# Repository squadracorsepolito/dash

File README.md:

Benvenuti nella repository ufficiale certificata contenente i file utilizzati per la scheda NuovaDash22© utilizzata dal team Squadra Corse Driverless nell'anno 2021/22

Repository mantenuta da Matteo Bonora (Software) e Francesco Minichelli (Hardware e Software)

## How to use the makefile
This project is generated to work with bare makefiles instead of the STM32CubeIDE. In order to successfully use the makefiles, you need to have a few tools installed. Refer to [this](https://www.bonnee.me/blog/stm32-vscode/) guide on how to setup your environment and install the needed tools (Visual Studio Code is optional and only needed to do debugging and to regenerate the makefile after regenerating code through STM32CubeMX).

If you want to **flash over CAN-bus**, you will need an [additional tool](https://github.com/arkku/srec) to convert the `.bin` firmware file to `.srec` and [bootcommander](https://www.feaser.com/openblt/doku.php?id=manual:bootcommander) to send the firmware to the dashboard.

### Build
In order to build the project, issue the following command:
`make -f STM32Make.make`
You can call `make clean` to clean the build directory.

### Flash
To configure the `can0` interface on your computer, you can call `make can` with root privileges.

`make canflash` will automatically convert the firmware to Motorola S-Record and pass it to bootcommander. If you only want to have the `.srec` file, you can call `make srec`

## Configurazione STM32CubeIDE per upload software tramite CAN

Project Properties -> C/C++ Build -> Settings -> Tool Settings -> MCU Post build outputs -> Selezionare "Convert to Motorola S-record file (-O ihex)"

### Run this command on the terminal to upload the code

1) Setup CAN0 interface with a Kvaser device connected to the PC Host
2a) Open MicroBoot
2b) Open BootCommander (same as MicroBoot but on a terminal)
3) Make sure the Target board is off and the can bus of the board connected to the Kvaser
  - There should be no problem if other device are connected on same can bus. If problem arises, turn off all other devices.
4a) Setup MicroBoot with the firmware to upload. 
4b) Lunch the terminal command
5) Power on the Target board.

```shell
cd /home/francesco/Desktop/openblt-master/Host
sudo ip link set can0 type can bitrate 1000000
sudo ip link set can0 up
./MicroBoot
```

La configurazione attuale è la seguente
CAN SPEED = 1Mbit
CAN message ID target-\>host = (0xFFA)
CAN message ID host-\>target = (0x007)

## Analisi NuovaDash22

I Micro attualmente utilizzati sono:
- STM32F303VCTx (256Kb version)
- STM32F303VETx (512Kb version)

Le periferiche attualmente utilizzate sono:
- CAN
- GPIO

Di seguito una descrizione (tensione, impedenza) per ogni pin del connettore in base all'uscita del micro.

| Signal Name  	| GPIO PIN SET 	 | GPIO PIN RESET | PIN NAME |
| ------------- | -------------- | -------------- | -------- |
| ASB CMD  	| ASB LED ON  	 | ASB LED OFF	  | PA8      |
| AMS CMD  	| AMS LED ON  	 | AMS LED OFF    | PC6      |
| IMD CMD  	| IMD LED ON  	 | IMD LED OFF    | PC8      |
| RTD CMD  	| RTD LED ON  	 | RTD LED OFF    | PC6      |
| TSOFF CMD  	| TSOFF LED ON 	 | TSOFF LED OFF  | PC11     |
| ASSI B CMD  	| ASSI B LED OFF | ASSI B LED ON  | PB8      |
| ASSI Y CMD  	| ASSI Y LED OFF | ASSI Y LED ON  | PB7      |
| AMI 1 CMD  	| AMI 1 LED OFF  | AMI 1 LED ON   | PB5      |
| AMI 2 CMD  	| AMI 2 LED OFF  | AMI 2 LED ON   | PD6      |
| AMI 3 CMD  	| AMI 3 LED OFF  | AMI 3 LED ON   | PD4      |

Appena la scheda parte, sia durante il bootloader che durante le prime fasi del programma (1 secondo di bootloader + [0-2.5 max] secondi di programma), al fine di rispettare la regola T11.9.5 che cito: 

> T 11.9.5 Indicators according to T 11.9.1 with safe state “illuminated” (e.g. absence of failures is not actively indicated) must be illuminated for 1 s to 3 s for visible check after power cycling the LVMS. 

ci si aspetta il seguente stato per ogni apparato della macchina:

- LED ASSI YELLOW (durante i test questo colore sarà BLU)
- LED AMI tutti accesi
- BuzzerAS Spento
- BuzzerEv Spento
- Cockpit tutto acceso tranne TSOFF

### Analisi Dashboard SC19

La scheda può essere suddivisa in 4 sezioni:

- MCU (STM32)
- Input/Output (Connettore)
- Alimentazione (DC/DC)
- Condizionamento Output/Input

### MCU (STM32)
Il micro utilizzato è un **STM32F303VCT**. 
- Alimentato con una tensione di 3.3V (ricavata tramite modulo DC/DC sulla scheda)
- Collegamento CAN con transreceiver SN65HVD234
- Connettore SWD
- Tre LED sulla scheda, RED/GREEN/BLUE, collegati rispettivamente ai pin PE11, PE12, PA3 e comandati tramite MOSFET (sulla scheda)
- GPIO (verranno spiegati in seguito)
  - PD10 : Imd\_Err\_Led\_Cmd
  - PE2: Buzzer\_CMD
  - PE3: No\_Hv\_Led\_CMD
  - PE5: Rtd\_Led\_CMD
  - PD13: PWM1
  - PD14: PWM2
  - PD15: PWM3
  - PA1: spare\_button
  - PA2: RTD\_button (RTD\_In)
  - PB9: BMS\_Led\_Cmd
- I2C
- USART
### Input/Output (Connettore)
### Alimentazione (DC/DC)
Input a 24V e output a 5V e 3.3V. Per la 5V è stato utilizzato un LMZ14202TZE e per la 3.3V un LM1117-3.3
### Condizionamento Output/Input
I seguenti segnali, provenienti dal connettore, sono collegati a un MOSFET con Source collegato a massa. Tra parentesi, il nome del GPIO della STM che controlla il mosfet
- IMD\_LED (IMD\_LED\_CMD)
- BMS\_LED (BMS\_LED\_CMD)
- RTD\_LED (RTD\_LED\_CMD)
- BUZZER (BUZZER\_CMD)
- No\_Hv\_Led (No\_Hv\_Led\_CMD)
- PUMP\_AUTO (PWM3)
- BP\_FAN\_AUTO (PWM2)
- RAD\_FAN\_AUTO (PWM1)

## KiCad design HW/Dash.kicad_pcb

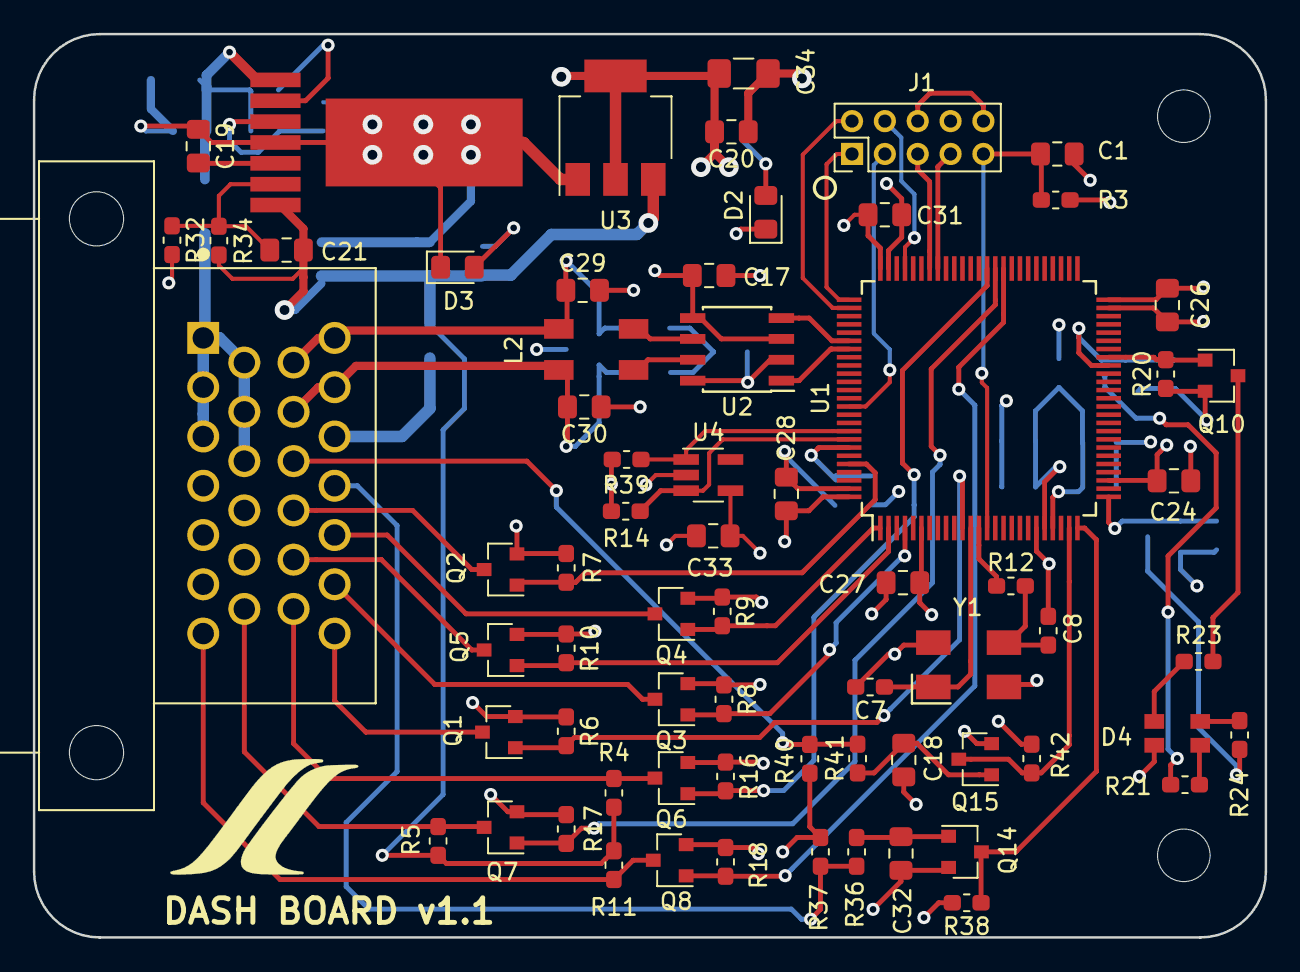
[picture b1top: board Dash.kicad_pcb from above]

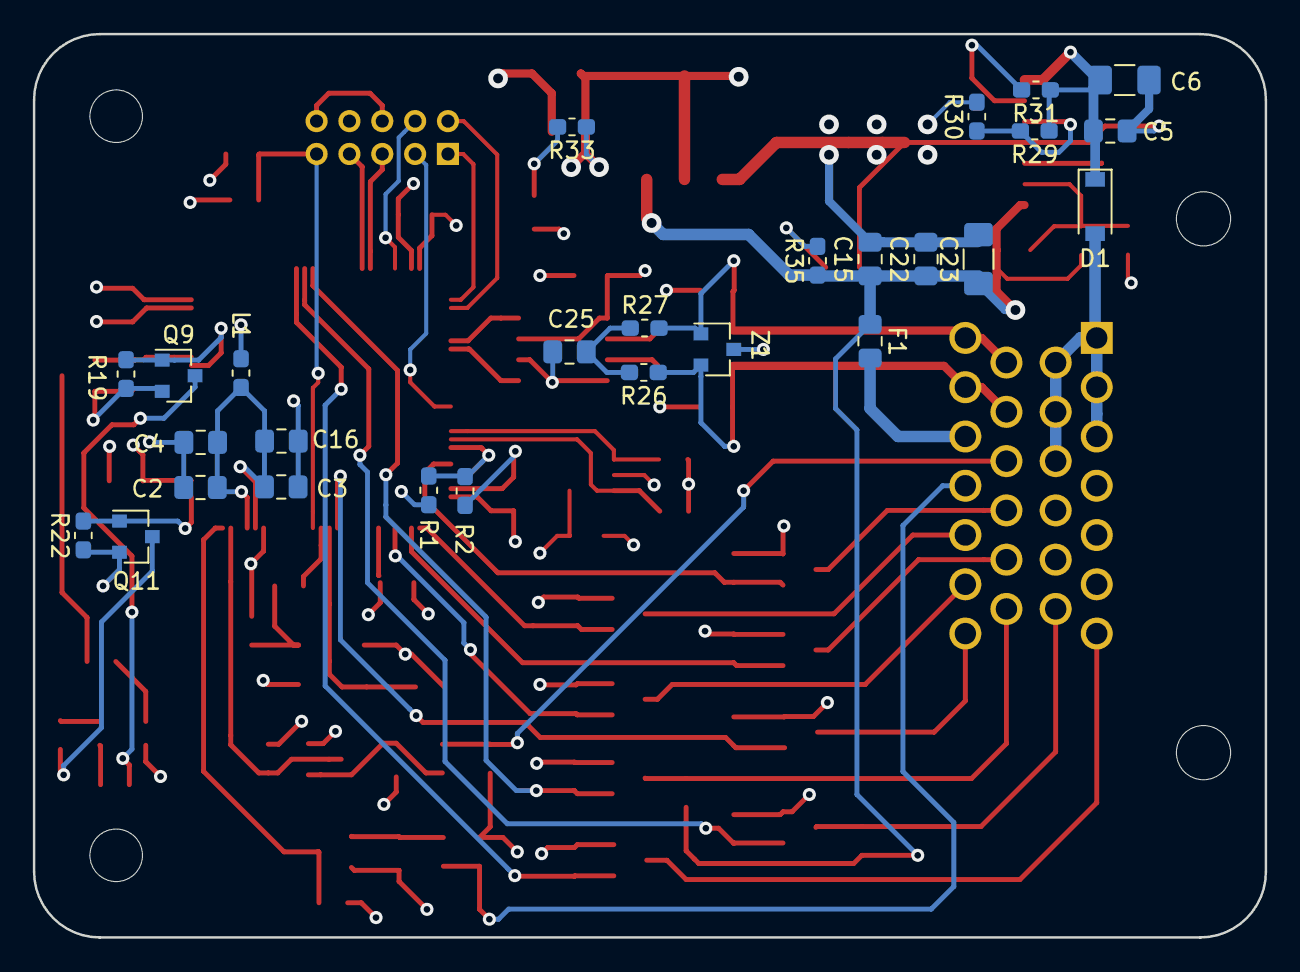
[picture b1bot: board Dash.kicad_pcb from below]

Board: 4 copper layers, 75.0 x 55.0 mm, 95 parts (27 on the bottom side), 64 nets.

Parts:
C1, C4, C16, C17, C18, C20, C24, C26, C27, C28, C32, C33: 100n; C_0805_2012Metric_Pad1.15x1.40mm_HandSolder
C2, C3, C5, C15, C22: 1u; C_0805_2012Metric_Pad1.15x1.40mm_HandSolder
C6, C34: 10u; C_1206_3216Metric_Pad1.42x1.75mm_HandSolder
C7, C8: 10p; C_0603_1608Metric_Pad1.05x0.95mm_HandSolder
C19, C21: 22n; C_0805_2012Metric_Pad1.15x1.40mm_HandSolder
C23: 100u; C_1206_3216Metric_Pad1.42x1.75mm_HandSolder
C25, C29, C30: 10p; C_0805_2012Metric_Pad1.15x1.40mm_HandSolder
C31: 4.7u; C_0805_2012Metric_Pad1.15x1.40mm_HandSolder
D1: D; D_SOD-123
D2, D3: LED; LED_0805_2012Metric_Pad1.15x1.40mm_HandSolder
D4: LED_RAGB; Kingbright PLCC4
F1: Fuse; Fuse_0805_2012Metric_Pad1.15x1.40mm_HandSolder
J1: Conn_02x05_Top_Bottom; Pin_Header_Straight_2x05_Pitch2.00mm
J2: Conn_02x13_Counter_Clockwise; TE_9-6437287-8
L1: L_Core_Ferrite; L_0603_1608Metric_Pad1.05x0.95mm_HandSolder
L2: L_Core_Ferrite_Coupled; ACT45B
Q1, Q2, Q3, Q4, Q5, Q6, Q7, Q8, Q9, Q10, Q11, Q14, Q15: Q_NMOS_GSD; SOT-23
R1: NM; R_0603_1608Metric_Pad1.05x0.95mm_HandSolder
R2, R16, R17, R18, R19, R20, R22: 33k; R_0603_1608Metric_Pad1.05x0.95mm_HandSolder
R3, R6, R7, R8, R9, R10, R31, R37, R40: 100k; R_0603_1608Metric_Pad1.05x0.95mm_HandSolder
R4, R5, R11: 3.3k; R_0603_1608Metric_Pad1.05x0.95mm_HandSolder
R12: 0; R_0603_1608Metric_Pad1.05x0.95mm_HandSolder
R14, R39: 3k; R_0603_1608Metric_Pad1.05x0.95mm_HandSolder
R21, R23, R24, R33, R35: 1.2k; R_0603_1608Metric_Pad1.05x0.95mm_HandSolder
R26, R27: 60; R_0603_1608Metric_Pad1.05x0.95mm_HandSolder
R29: 68.1k; R_0603_1608Metric_Pad1.05x0.95mm_HandSolder
R30: 11.8k; R_0603_1608Metric_Pad1.05x0.95mm_HandSolder
R32: 1.07k; R_0603_1608Metric_Pad1.05x0.95mm_HandSolder
R34: 5.62k; R_0603_1608Metric_Pad1.05x0.95mm_HandSolder
R36, R38, R41, R42: 15k; R_0603_1608Metric_Pad1.05x0.95mm_HandSolder
U1: STM32F303VCTx; LQFP-100_14x14mm_P0.5mm
U2: SN65HVD234; SOIC-8_3.9x4.9mm_P1.27mm
U3: LM1117-3.3; SOT-223
U4: 24AA02-OT; SOT-23-5_HandSoldering
U5: LMZ14202TZE-ADJ_NOPB; TO-PMOD-7
Y1: Crystal_GND24; Crystal_SMD_Abracon_ABM3B-4Pin_5.0x3.2mm
Z1: PESD2CAN,215; SOT-23

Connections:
+3V3: C17.2, C20.2, C24.1, C26.1, C27.1, C28.1, C31.1, C33.1, C34.1, D4.2, J1.6, J1.10, L1.2, R1.2, R3.2, R14.2, R33.1, R37.2, R38.2, R39.2, R40.2, R42.2, U1.6, U1.28, U1.50, U1.75, U1.100, U2.3, U2.5, U3.2, U3.4, U4.4
+5V: C15.1, C21.1, C22.1, C23.1, F1.1, R4.2, R5.2, R11.2, R34.2, R35.1, U3.3, U5.7
/+24v: D1.2, J2.1, J2.2, J2.3, J2.8, J2.9, J2.10
/BMS_LED: J2.17, Q2.3
/BUZ: J2.24, Q4.3
/CAN_H: C30.2, J2.15, J2.21, L2.4, R26.1, Z1.2
/CAN_L: C29.1, J2.14, J2.20, L2.3, R27.1, Z1.1
/Cockpit management/BMS_LED_CMD: Q2.1, R7.2, U1.96
/Cockpit management/BUZZER_CMD: Q4.1, R9.2, U1.1
/Cockpit management/IMD_LED_CMD: Q1.1, R6.2, U1.11
/Cockpit management/NO_HV_LED_CMD: Q5.1, R10.2, U1.2
/Cockpit management/PWM1: Q8.1, R18.2, U1.60
/Cockpit management/PWM2: Q7.1, R17.2, U1.61
/Cockpit management/PWM3: Q6.1, R16.2, U1.62
/Cockpit management/RTD_LED_CMD: Q3.1, R8.2, U1.4
/Cockpit management/Spare_Button: Q15.3, R42.1, U1.24
/HV_LED: J2.18, Q5.3
/IMD_LED: J2.26, Q1.3
/MCU/CAN_RX: U1.81, U2.4
/MCU/CAN_TX: U1.82, U2.1
/MCU/JTDI: J1.2, U1.77
/MCU/NRST: C1.1, J1.9, R3.1, U1.14
/MCU/RTD_Button: Q14.3, R38.1, U1.25
/MCU/SCL: R39.1, U1.92, U4.1
/MCU/SDA: R14.1, U1.93, U4.3
/MCU/SWCLK: J1.1, U1.76
/MCU/SWDIO: J1.4, U1.72
/MCU/SWO: J1.3, U1.89
/MCU/USART_RX: J1.5, U1.69
/MCU/USART_TX: J1.7, U1.68
/MCU/VDD_A: C2.1, C3.1, C4.1, C16.1, L1.1, U1.21, U1.22
/MCU/gpio_BLUE: Q11.1, R22.2, U1.26
/MCU/gpio_GREEN: Q10.1, R20.2, U1.43
/MCU/gpio_RED: Q9.1, R19.2, U1.42
/PWM1: J2.7, Q8.3, R11.1
/PWM2: J2.13, Q7.3, R5.1
/PWM3: J2.19, Q6.3, R4.1
/RTD: J2.23, R36.2, R37.1
/RTD_LED: J2.25, Q3.3
/Spare_butt: J2.16, R40.1, R41.2
GND: C1.2, C2.2, C3.2, C4.2, C5.2, C6.2, C7.2, C8.2, C15.2, C16.2, C17.1, C18.2, C19.1, C20.1, C22.2, C23.2, C24.2, C25.2, C26.2, C27.2, C28.2, C29.2, C30.1, C31.2, C32.2, C33.2, C34.2, D2.1, D3.1, J1.8, J2.4, J2.5, J2.6, J2.11, J2.12, Q1.2, Q2.2, Q3.2, Q4.2, Q5.2, Q6.2, Q7.2, Q8.2, Q9.2, Q10.2, Q11.2, Q14.2, Q15.2, R2.1, R6.1, R7.1, R8.1, R9.1, R10.1, R16.1, R17.1, R18.1, R19.1, R20.1, R22.1, R30.2, R32.2, U1.20, U1.49, U1.74, U1.99, U2.2, U2.8, U3.1, U4.2, U5.4, Y1.2, Y1.4, Z1.3
unnamed: C5.1, C6.1, D1.1, R29.1, R31.1, U5.1
unnamed: C7.1, U1.12, Y1.1
unnamed: C8.1, R12.2, Y1.3
unnamed: C18.1, Q15.1, R41.1
unnamed: C19.2, U5.5
unnamed: C21.2, R32.1, R34.1, U5.6
unnamed: C25.1, R26.2, R27.2
unnamed: C32.1, Q14.1, R36.1
unnamed: D2.2, R33.2
unnamed: D3.2, R35.2
unnamed: D4.1, R21.2
unnamed: D4.3, R23.2
unnamed: D4.4, R24.1
unnamed: F1.2, J2.22
unnamed: L2.1, U2.7
unnamed: L2.2, U2.6
unnamed: Q9.3, R21.1
unnamed: Q10.3, R23.1
unnamed: Q11.3, R24.2
unnamed: R1.1, R2.2, U1.94
unnamed: R12.1, U1.13
unnamed: R29.2, R30.1, U5.3
unnamed: R31.2, U5.2

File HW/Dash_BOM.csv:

DASH_BOM


"Component Count:","98"

"C2, C3, C22, C5, C15, 														",	"5",	"1u",			"C","Capacitors_SMD:C_0805","Unpolarized capacitor",""
"C6, 																		",	"1",	"10u",			"C","Capacitors_SMD:C_1206","Unpolarized capacitor",""
"C21, C19, 																	",	"2",	"22n",			"C","Capacitors_SMD:C_0805","Unpolarized capacitor",""
"C23, 																		",	"1",	"100u",			"C","Capacitors_SMD:C_1210","Unpolarized capacitor",""
"C25, C29, C30, 															",	"3",	"10p",			"C","Capacitors_SMD:C_0805","Unpolarized capacitor",""
"C28, C27, C26, C24, C4, C16, C1, C17, C20, C32, C18, C33, 					",	"12",	"100n",			"C","Capacitors_SMD:C_0805","Unpolarized capacitor",""
"C31, 																		",	"1",	"4.7u",			"C","Capacitors_SMD:C_0805","Unpolarized capacitor",""
"C34, 																		",	"1",	"10u",			"C","Capacitors_SMD:C_0805","Unpolarized capacitor",""
"D1, 																		",	"1",	"D",			"D","Diodes_SMD:D_SOD-123","Diode",""
"D3, D2, 																	",	"2",	"LED", 			"LED","Diodes_SMD:D_0805","Light emitting diode",""
"D4, 																		",	"1",	"LED_RAGB",		"LED_RAGB","footprint:Kingbright PLCC4","RGB LED, red/anode/green/blue",""
"FL1, 																		",	"1",	"ACT45B-220-2P-TL003","ACT45B-220-2P-TL003-ACT45B-220-2P-TL003","footprint:ACT45B","",""
"J1, 																		",	"1",	"Conn_02x05_Top_Bottom",		
"J2, 																		",	"1",	"souriau18pin",	"souriau18pin-Connector","footprint:8STA1418","",""
"L1, 																		",	"1",	"L_Core_Ferrite",	"L_Core_Ferrite","Inductors_SMD:L_0603","Inductor with ferrite core",""
"Q9, Q10, Q11, Q14, Q1, Q2, Q3, Q4, Q5, Q6, Q7, Q8, Q15, 					",	"13",	"Q_NMOS_GSD",	"Q_NMOS_GSD","TO_SOT_Packages_SMD:SOT-323_SC-70","N-MOSFET transistor,
"Q12, 																		",	"1",	"BC857BDW1",	"BC857BDW1","TO_SOT_Packages_SMD:SOT-363_SC-70-6","100mA IC, 45V Vce, 
"Q13, 																		",	"1",	"Q_PMOS_GSD",	"Q_PMOS_GSD","TO_SOT_Packages_SMD:SOT-323_SC-70","P-MOSFET transistor, 
"R1, 																		",	"1",	"NM","R_US",	"Resistors_SMD:R_0603","Resistor, US symbol",""
"R2, R36, R38, R41, R42, 													",	"5",	"15k",	"R",	"Resistors_SMD:R_0603","Resistor",""
"R3, R19, R20, R22, R6, R7, R8, R9, R10, R16, R17, R18, R37, R40, R31, 		",	"15",	"100k",			"R","Resistors_SMD:R_0603","Resistor",""
"R13, R12, R11, R5, R4, R15, 												",	"6",	"22",			"R_US","Resistors_SMD:R_0603","Resistor, US symbol",""
"R14, R39, 																	",	"2",	"2k",			"R_US","Resistors_SMD:R_0603","Resistor, US symbol",""
"R21, 																		",	"1",	"1.6k",			"R_US","Resistors_SMD:R_0603","Resistor, US symbol",""
"R23, R24, R35, R33, 														",	"4",	"1.2k",			"R","Resistors_SMD:R_0603","Resistor",""
"R25, R28, R29, 															",	"3",	"68.1k",		"R","Resistors_SMD:R_0603","Resistor",""
"R27, R26, 																	",	"2",	"60",			"R_US","Resistors_SMD:R_0603","Resistor, US symbol",""
"R30, 																		",	"1",	"11.8k",		"R","Resistors_SMD:R_0603","Resistor",""
"R32, 																		",	"1",	"1.07k",		"R","Resistors_SMD:R_0603","Resistor",""
"R34, 																		",	"1",	"5.62k",		"R","Resistors_SMD:R_0603","Resistor",""
"SW1, 																		",	"1",	"SW_Push_Dual",	"SW_Push_Dual","footprint:pulsante","Push button switch
"U1, 																		",	"1",	"STM32F303VCTx","STM32F303VCTx","Housings_QFP:LQFP-100_14x14mm_Pitch0.5mm",
"U2, 																		",	"1",	"SN65HVD234",	"SN65HVD234","CAN Bus Transceiver,
"U3, 																		",	"1",	"LM1117-3.3",	"LM1117-3.3-Regulator_Linear","TO_SOT_Packages_SMD:SOT-223","",""
"U4, 																		",	"1",	"24AA02-OT",	"24AA02-OT","TO_SOT_Packages_SMD:SOT-23-5","I2C Serial EEPROM, 2Kb, SOT-23",""
"U5, 																		",	"1",	"LMZ14202TZE-ADJ_NOPB","LMZ14202TZE-ADJ_NOPB-LMZ14202TZE-ADJ_NOPB","footprint:TO-PMOD-7","",""
"Z1, 																		",	"1",	"PESD2CAN,215",	"PESD2CAN,215-PESD2CAN_215","TO_SOT_Packages_SMD:SOT-23","",""

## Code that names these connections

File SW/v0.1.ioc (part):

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Mcu.Name=STM32F303V(B-C)Tx
Mcu.Package=LQFP100
Mcu.UserName=STM32F303VCTx
PA0.GPIOParameters=GPIO_Label
PA0.GPIO_Label=RTD_BUTTON
PA0.Signal=GPIO_Input
PA10.Mode=Asynchronous
PA10.Signal=USART1_RX
PA13.Mode=Serial_Wire
PA13.Signal=SYS_JTMS-SWDIO
PA14.Mode=Serial_Wire
PA14.Signal=SYS_JTCK-SWCLK
PA15.Signal=SYS_JTDI
PA9.Mode=Asynchronous
PA9.Signal=USART1_TX
PB10.GPIOParameters=GPIO_Label
PB10.GPIO_Label=RTD_LED
PB10.Signal=GPIO_Output
PB3.Signal=SYS_JTDO-TRACESWO
PC2.GPIOParameters=GPIO_Label
PC2.GPIO_Label=SPARE_IN
PC2.Signal=GPIO_Input
PD0.GPIOParameters=GPIO_PuPd
PD0.GPIO_PuPd=GPIO_PULLDOWN
PD0.Mode=Master
PD0.Signal=CAN_RX
PD1.GPIOParameters=GPIO_PuPd
PD1.GPIO_PuPd=GPIO_PULLDOWN
PD1.Mode=Master
PD1.Signal=CAN_TX
PD13.GPIOParameters=GPIO_ModeDefaultPP,GPIO_Speed,GPIO_PuPd,GPIO_Label
PD13.GPIO_Label=PWM_PUMP
PD13.GPIO_ModeDefaultPP=GPIO_MODE_AF_PP
PD13.GPIO_PuPd=GPIO_NOPULL
PD13.GPIO_Speed=GPIO_SPEED_FREQ_HIGH
PD13.Signal=S_TIM4_CH2
PD14.GPIOParameters=GPIO_ModeDefaultPP,GPIO_Speed,GPIO_PuPd,GPIO_Label
PD14.GPIO_Label=PWM_RAD_FAN
PD14.GPIO_ModeDefaultPP=GPIO_MODE_AF_PP
PD14.GPIO_PuPd=GPIO_NOPULL
PD14.GPIO_Speed=GPIO_SPEED_FREQ_HIGH
PD14.Signal=S_TIM4_CH3
PD15.GPIOParameters=GPIO_Label
PD15.GPIO_Label=BP_FAN
PD15.Signal=GPIO_Output
PE10.GPIOParameters=GPIO_Label
PE10.GPIO_Label=BMS_LED
PE10.Signal=GPIO_Output
PE12.GPIOParameters=GPIO_Label
PE12.GPIO_Label=NOHV_LED
PE12.Signal=GPIO_Output
PE14.GPIOParameters=GPIO_Label
PE14.GPIO_Label=IMD_LED
PE14.Signal=GPIO_Output
PE15.GPIOParameters=GPIO_Label
PE15.GPIO_Label=BUZZER
PE15.Signal=GPIO_Output
PE2.GPIOParameters=GPIO_Label
PE2.GPIO_Label=LED_R
PE2.Signal=GPIO_Output
PE4.GPIOParameters=GPIO_Label
PE4.GPIO_Label=LED_G
PE4.Signal=GPIO_Output
PF1-OSC_OUT.GPIOParameters=GPIO_Label
PF1-OSC_OUT.GPIO_Label=LED_B
PF1-OSC_OUT.Signal=GPIO_Output
RCC.HSEPLLFreq_Value=8000000
RCC.HSE_VALUE=8000000
RCC.SYSCLKFreq_VALUE=60000000
RCC.SYSCLKSourceVirtual=RCC_SYSCLKSOURCE_PLLCLK
board=v0.1.1

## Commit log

2021-12-01 First commit - v 1.0
    First commit
2021-12-02 Version 1.1
    Version 1.1
    Hw and Sw improvements
2022-04-26 Add new requirements
2022-04-29 Initial dash22 build
2022-04-30 Split peripherals in multiple files
2022-04-30 Add button debouncing functions
2022-05-02 Update
    Aggiornamenti dopo riunione 02/05
2022-05-04 Check both RTD buttons and wire up ERROR state. Partially fixes #4
2022-05-08 Add AMI LED support. Adds ami.c/.h files that handle the mission LEDs as described by #9
2022-05-26 Add AS FSM Fixes #8
2022-05-30 Wire up CAN message for AS state. Fixes #8
2022-05-31 First working test
2022-05-31 Fix debouncing
2022-05-31 Deleted HW, openBLT folder. Added new openBLT
    The HW files and openBLT were out of date. Added the new openBLT
2022-05-31 Moved BOOT_BACKDOOR_ENTRY_TIMEOUT
2022-05-31 Set Clock to 72 and changed CAN ID
2022-05-31 Minor changes
2022-05-31 removed Debug folder
2022-06-02 Move CAN-related functions to can.c
2022-06-02 Add comments and clean old code
2022-06-06 Add autonomous mission status CAN message. Should close #9
2022-06-06 Add EBS relay command via CAN
2022-06-07 First in-car test
2022-06-07 Fix button_get(), remove ASMS stuff
2022-06-09 Rename and refactor ami to mission
2022-06-10 Add can watchdog
2022-06-10 Fix mission sorting
2022-06-12 Small fixes to button and mission
2022-06-12 Tidy up init state
2022-06-13 Configure timers for cooling and ASB
2022-06-15 Move init state outside the rtd fsm
2022-06-15 Setup ASB timer and CAN message
2022-06-15 [WDG] wait for dSpace to boot
2022-06-15 Move comments around
2022-06-15 Small fixes
2022-06-16 Update CAN IDs
2022-06-23 Overhaul fsm after preliminary tests with dSpace
2022-06-24 ( ͡° ͜ʖ ͡°)
2022-06-24 Clean
2022-06-24 Add tentative flow chart
2022-06-24 Add updated dbc definition
2022-06-24 Follow the flow chart
2022-06-24 Reset all flags after each FSM cycle. Closes #15
2022-06-24 Fix minor bug on button.c and decouple logical and physical states
2022-06-24 Document watchdog
2022-06-24 Minor cleanups
2022-06-27 Add local drivers to avoid absolute paths in makefile
2022-06-27 Add little documentation on makefiles
2022-06-30 Initial release of dash22v2
2022-06-30 Fix PWM signals for cooling and ASB
2022-07-05 Port bootloader to new MCU (tentative)
2022-07-06 Add bit-banged pwm signal for inverter pumps Sventura a te, Francesco Minichelli
2022-07-07 Blink AMI when mission is not confirmed (judges are gonna LOVE this)
2022-07-07 Engineers keep complaining about this
2022-07-07 Bump cubemx version
2022-07-07 Add most important mission
2022-07-07 Add rtd beep. Ma tanto la dspace non mi manda gli ack ¯\_(ツ)_/¯
2022-07-10 Remove useless mission. Enable RTD sound with AS buzzer
2022-07-11 Fix conflicts when different systems share the same buzzer
2022-07-18 Test both assi colors at startup
2022-07-21 Add new dash logo
2022-08-21 Rename acceleration mission to a more meaningful name
2022-09-26 Improve comments
2023-06-28 fix: now working bootloader
2023-06-30 chore: stuff
2023-06-30 chore: restored error state on wdg
2023-07-09 chore: added SCan submodule
2023-07-09 chore: removed RTD fsm
2023-07-09 fix: blink period in tson
2023-07-24 feat: updated rtd fsm to open shutdown in discharge
2024-06-17 feat: autobus-off management
